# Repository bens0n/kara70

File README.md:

# kara70
70% FRL TKL keyboard assembled with primarily through hole components, including usb type-c. Inspired by cftkb [discipline](https://github.com/coseyfannitutti/discipline) and [mysterium](https://github.com/coseyfannitutti/mysterium), and also envious' [delirium](https://github.com/Envious-Data/Env-KB). 

The microcontroller has been updated from an atmega to an RP2040, which is mounted on the back-side to maintain the through-hole look. A slightly unnecessary logic shifter does double duty as a pretend through-hole controller. Underglow RGB has been added, and a minimal (LED diffusing) case connects the base to the plate.

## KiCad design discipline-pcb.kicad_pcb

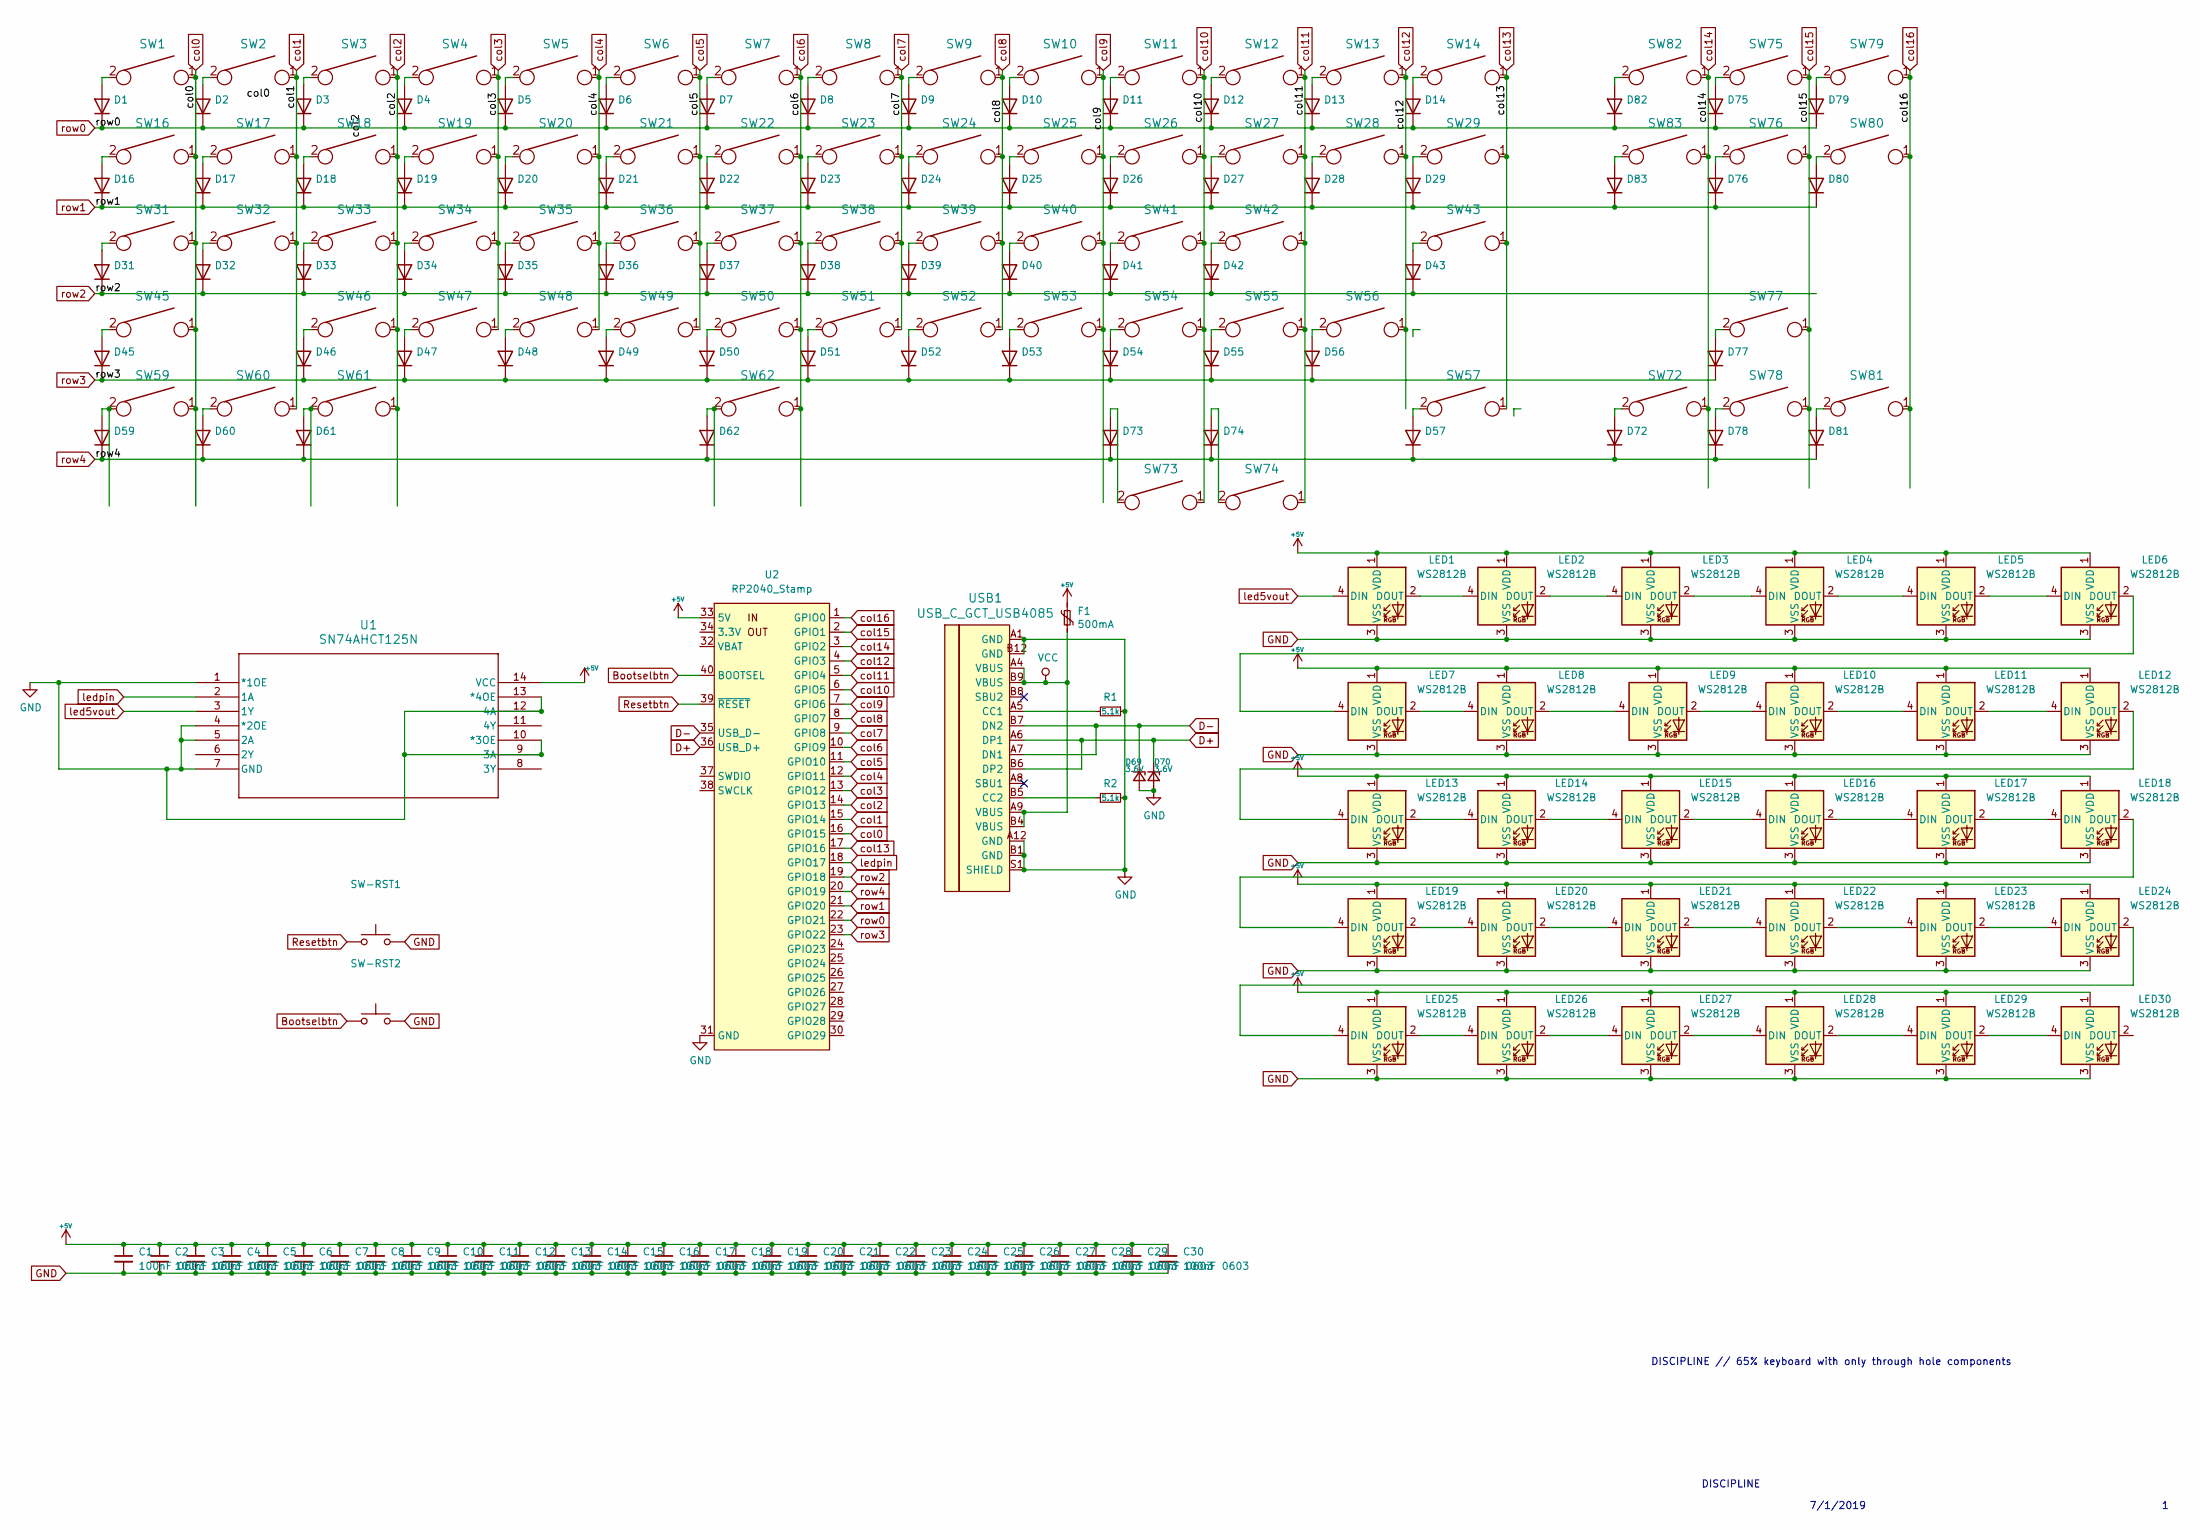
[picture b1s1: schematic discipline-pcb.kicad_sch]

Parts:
C1, C2, C3, C4, C5, C6, C7, C8, C9, C10, C11, C12, C13, C14, C15, C16, C17, C18, C19, C20, C21, C22, C23, C24, C25, C26, C27, C28, C29, C30: 100nF 0603; C_0603_1608Metric_Pad1.08x0.95mm_HandSolder
D1, D2, D3, D4, D5, D6, D7, D8, D9, D10, D11, D12, D13, D14, D16, D17, D18, D19, D20, D21, D22, D23, D24, D25, D26, D27, D28, D29, D31, D32, D33, D34, D35, D36, D37, D38, D39, D40, D41, D42, D43, D45, D46, D47, D48, D49, D50, D51, D52, D53, D54, D55, D56, D57, D59, D60, D61, D62, D72, D73, D74, D75, D76, D77, D78, D79, D80, D81, D82, D83: D_DO-35_SOD27_P5.08mm_Horizontal
D69, D70: 3.6V; D_DO-35_SOD27_P5.08mm_Horizontal
F1: 500mA; polyfuse_5.1mm
LED1, LED2, LED3, LED4, LED5, LED6, LED7, LED8, LED9, LED10, LED11, LED12, LED13, LED14, LED15, LED16, LED17, LED18, LED19, LED20, LED21, LED22, LED23, LED24, LED25, LED26, LED27, LED28, LED29, LED30: WS2812B; LED_WS2812B_PLCC4_5.0x5.0mm_P3.2mm
R1, R2: 5.1k; R_Axial_DIN0204_L3.6mm_D1.6mm_P7.62mm_Horizontal
SW1, SW2, SW3, SW4, SW5, SW6, SW7, SW8, SW9, SW10, SW11, SW12, SW13, SW17, SW18, SW19, SW20, SW21, SW22, SW23, SW24, SW25, SW26, SW27, SW28, SW32, SW33, SW34, SW35, SW36, SW37, SW38, SW39, SW40, SW41, SW42, SW46, SW47, SW48, SW49, SW50, SW51, SW52, SW53, SW54, SW55, SW72, SW75, SW76, SW77, SW78, SW79, SW80, SW81, SW82, SW83: KEYSW; MX-Hotswap-1U
SW14: KEYSW; MX-Hotswap-2U
SW16, SW29, SW73, SW74: KEYSW; MX-Hotswap-1.5U
SW31: KEYSW; MX-Hotswap-1.75U
SW43, SW45: KEYSW; MX-Hotswap-2.25U
SW56: KEYSW; MX-Hotswap-2.75U
SW57, SW59, SW60, SW61: KEYSW; MX-Hotswap-1.25U
SW62: KEYSW; MX-Hotswap-7U-ReversedStabilizers
SW-RST1, SW-RST2: SW_PUSH_6mm
U1: SN74AHCT125N; N14
U2: RP2040_Stamp; RP2xxx_Stamp_SMD
USB1: USB_C_GCT_USB4085

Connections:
+5V: C1.1, C2.1, C3.1, C4.1, C5.1, C6.1, C7.1, C8.1, C9.1, C10.1, C11.1, C12.1, C13.1, C14.1, C15.1, C16.1, C17.1, C18.1, C19.1, C20.1, C21.1, C22.1, C23.1, C24.1, C25.1, C26.1, C27.1, C28.1, C29.1, C30.1, F1.1, LED1.1 (VDD), LED2.1 (VDD), LED3.1 (VDD), LED4.1 (VDD), LED5.1 (VDD), LED6.1 (VDD), LED7.1 (VDD), LED8.1 (VDD), LED9.1 (VDD), LED10.1 (VDD), LED11.1 (VDD), LED12.1 (VDD), LED13.1 (VDD), LED14.1 (VDD), LED15.1 (VDD), LED16.1 (VDD), LED17.1 (VDD), LED18.1 (VDD), LED19.1 (VDD), LED20.1 (VDD), LED21.1 (VDD), LED22.1 (VDD), LED23.1 (VDD), LED24.1 (VDD), LED25.1 (VDD), LED26.1 (VDD), LED27.1 (VDD), LED28.1 (VDD), LED29.1 (VDD), LED30.1 (VDD), U1.14 (VCC), U2.33 (5V)
Bootselbtn: SW-RST2.1, U2.40 (BOOTSEL)
D+: D70.1 (K), U2.36 (USB_D+), USB1.A6 (DP1), USB1.B6 (DP2)
D-: D69.1 (K), U2.35 (USB_D-), USB1.A7 (DN1), USB1.B7 (DN2)
GND: C1.2, C2.2, C3.2, C4.2, C5.2, C6.2, C7.2, C8.2, C9.2, C10.2, C11.2, C12.2, C13.2, C14.2, C15.2, C16.2, C17.2, C18.2, C19.2, C20.2, C21.2, C22.2, C23.2, C24.2, C25.2, C26.2, C27.2, C28.2, C29.2, C30.2, D69.2 (A), D70.2 (A), LED1.3 (VSS), LED2.3 (VSS), LED3.3 (VSS), LED4.3 (VSS), LED5.3 (VSS), LED6.3 (VSS), LED7.3 (VSS), LED8.3 (VSS), LED9.3 (VSS), LED10.3 (VSS), LED11.3 (VSS), LED12.3 (VSS), LED13.3 (VSS), LED14.3 (VSS), LED15.3 (VSS), LED16.3 (VSS), LED17.3 (VSS), LED18.3 (VSS), LED19.3 (VSS), LED20.3 (VSS), LED21.3 (VSS), LED22.3 (VSS), LED23.3 (VSS), LED24.3 (VSS), LED25.3 (VSS), LED26.3 (VSS), LED27.3 (VSS), LED28.3 (VSS), LED29.3 (VSS), LED30.3 (VSS), R1.1, R2.2, SW-RST1.2, SW-RST2.2, U1.1 (*1OE), U1.4 (*2OE), U1.5 (2A), U1.7 (GND), U1.9 (3A), U1.10 (*3OE), U1.12 (4A), U1.13 (*4OE), U2.31 (GND), USB1.A1 (GND), USB1.A12 (GND), USB1.B1 (GND), USB1.B12 (GND), USB1.S1 (SHIELD)
unnamed: D1.2 (A), SW1.2
unnamed: D2.2 (A), SW2.2
unnamed: D3.2 (A), SW3.2
unnamed: D4.2 (A), SW4.2
unnamed: D5.2 (A), SW5.2
unnamed: D6.2 (A), SW6.2
unnamed: D7.2 (A), SW7.2
unnamed: D8.2 (A), SW8.2
unnamed: D9.2 (A), SW9.2
unnamed: D10.2 (A), SW10.2
unnamed: D11.2 (A), SW11.2
unnamed: D12.2 (A), SW12.2
unnamed: D13.2 (A), SW13.2
unnamed: D14.2 (A), SW14.2
unnamed: D16.2 (A), SW16.2
unnamed: D17.2 (A), SW17.2
unnamed: D18.2 (A), SW18.2
unnamed: D19.2 (A), SW19.2
unnamed: D20.2 (A), SW20.2
unnamed: D21.2 (A), SW21.2
unnamed: D22.2 (A), SW22.2
unnamed: D23.2 (A), SW23.2
unnamed: D24.2 (A), SW24.2
unnamed: D25.2 (A), SW25.2
unnamed: D26.2 (A), SW26.2
unnamed: D27.2 (A), SW27.2
unnamed: D28.2 (A), SW28.2
unnamed: D29.2 (A), SW29.2
unnamed: D31.2 (A), SW31.2
unnamed: D32.2 (A), SW32.2
unnamed: D33.2 (A), SW33.2
unnamed: D34.2 (A), SW34.2
unnamed: D35.2 (A), SW35.2
unnamed: D36.2 (A), SW36.2
unnamed: D37.2 (A), SW37.2
unnamed: D38.2 (A), SW38.2
unnamed: D39.2 (A), SW39.2
unnamed: D40.2 (A), SW40.2
unnamed: D41.2 (A), SW41.2
unnamed: D42.2 (A), SW42.2
unnamed: D43.2 (A), SW43.2
unnamed: D45.2 (A), SW45.2
unnamed: D46.2 (A), SW46.2
unnamed: D47.2 (A), SW47.2
unnamed: D48.2 (A), SW48.2
unnamed: D49.2 (A), SW49.2
unnamed: D50.2 (A), SW50.2
unnamed: D51.2 (A), SW51.2
unnamed: D52.2 (A), SW52.2
unnamed: D53.2 (A), SW53.2
unnamed: D54.2 (A), SW54.2
unnamed: D55.2 (A), SW55.2
unnamed: D56.2 (A), SW56.2
unnamed: D57.2 (A), SW57.2
unnamed: D59.2 (A), SW59.2
unnamed: D60.2 (A), SW60.2
unnamed: D61.2 (A), SW61.2
unnamed: D62.2 (A), SW62.2
unnamed: D72.2 (A), SW72.2
unnamed: D73.2 (A), SW73.2
unnamed: D74.2 (A), SW74.2
unnamed: D75.2 (A), SW75.2
unnamed: D76.2 (A), SW76.2
unnamed: D77.2 (A), SW77.2
unnamed: D78.2 (A), SW78.2
unnamed: D79.2 (A), SW79.2
unnamed: D80.2 (A), SW80.2
unnamed: D81.2 (A), SW81.2
unnamed: D82.2 (A), SW82.2
unnamed: D83.2 (A), SW83.2
unnamed: LED1.2 (DOUT), LED2.4 (DIN)
unnamed: LED2.2 (DOUT), LED3.4 (DIN)
unnamed: LED3.2 (DOUT), LED4.4 (DIN)
unnamed: LED4.2 (DOUT), LED5.4 (DIN)
unnamed: LED5.2 (DOUT), LED6.4 (DIN)
unnamed: LED6.2 (DOUT), LED7.4 (DIN)
unnamed: LED7.2 (DOUT), LED8.4 (DIN)
unnamed: LED8.2 (DOUT), LED9.4 (DIN)
unnamed: LED9.2 (DOUT), LED10.4 (DIN)
unnamed: LED10.2 (DOUT), LED11.4 (DIN)
unnamed: LED11.2 (DOUT), LED12.4 (DIN)
unnamed: LED12.2 (DOUT), LED13.4 (DIN)
unnamed: LED13.2 (DOUT), LED14.4 (DIN)
unnamed: LED14.2 (DOUT), LED15.4 (DIN)
unnamed: LED15.2 (DOUT), LED16.4 (DIN)
unnamed: LED16.2 (DOUT), LED17.4 (DIN)
unnamed: LED17.2 (DOUT), LED18.4 (DIN)
unnamed: LED18.2 (DOUT), LED19.4 (DIN)
unnamed: LED19.2 (DOUT), LED20.4 (DIN)
unnamed: LED20.2 (DOUT), LED21.4 (DIN)
unnamed: LED21.2 (DOUT), LED22.4 (DIN)
unnamed: LED22.2 (DOUT), LED23.4 (DIN)
unnamed: LED23.2 (DOUT), LED24.4 (DIN)
unnamed: LED24.2 (DOUT), LED25.4 (DIN)
unnamed: LED25.2 (DOUT), LED26.4 (DIN)
unnamed: LED26.2 (DOUT), LED27.4 (DIN)
unnamed: LED27.2 (DOUT), LED28.4 (DIN)
unnamed: LED28.2 (DOUT), LED29.4 (DIN)
unnamed: LED29.2 (DOUT), LED30.4 (DIN)
unnamed: R1.2, USB1.A5 (CC1)
unnamed: R2.1, USB1.B5 (CC2)
Resetbtn: SW-RST1.1, U2.39 (~RESET)
VCC: F1.2, USB1.A4 (VBUS), USB1.A9 (VBUS), USB1.B4 (VBUS), USB1.B9 (VBUS)
col0: SW1.1, SW16.1, SW31.1, SW45.1, SW59.1, U2.16 (GPIO15)
col1: SW2.1, SW17.1, SW32.1, SW60.1, U2.15 (GPIO14)
col2: SW3.1, SW18.1, SW33.1, SW46.1, SW61.1, U2.14 (GPIO13)
col3: SW4.1, SW19.1, SW34.1, SW47.1, U2.13 (GPIO12)
col4: SW5.1, SW20.1, SW35.1, SW48.1, U2.12 (GPIO11)
col5: SW6.1, SW21.1, SW36.1, SW49.1, U2.11 (GPIO10)
col6: SW7.1, SW22.1, SW37.1, SW50.1, SW62.1, U2.10 (GPIO9)
col7: SW8.1, SW23.1, SW38.1, SW51.1, U2.9 (GPIO8)
col8: SW9.1, SW24.1, SW39.1, SW52.1, U2.8 (GPIO7)
col9: SW10.1, SW25.1, SW40.1, SW53.1, U2.7 (GPIO6)
col10: SW11.1, SW26.1, SW41.1, SW54.1, SW73.1, U2.6 (GPIO5)
col11: SW12.1, SW27.1, SW42.1, SW55.1, SW74.1, U2.5 (GPIO4)
col12: SW13.1, SW28.1, SW56.1, U2.4 (GPIO3)
col13: SW14.1, SW29.1, SW43.1, SW57.1, U2.17 (GPIO16)
col14: SW72.1, SW82.1, SW83.1, U2.3 (GPIO2)
col15: SW75.1, SW76.1, SW77.1, SW78.1, U2.2 (GPIO1)
col16: SW79.1, SW80.1, SW81.1, U2.1 (GPIO0)
led5vout: LED1.4 (DIN), U1.3 (1Y)
ledpin: U1.2 (1A), U2.18 (GPIO17)
row0: D1.1 (K), D2.1 (K), D3.1 (K), D4.1 (K), D5.1 (K), D6.1 (K), D7.1 (K), D8.1 (K), D9.1 (K), D10.1 (K), D11.1 (K), D12.1 (K), D13.1 (K), D14.1 (K), D75.1 (K), D79.1 (K), D82.1 (K), U2.22 (GPIO21)
row1: D16.1 (K), D17.1 (K), D18.1 (K), D19.1 (K), D20.1 (K), D21.1 (K), D22.1 (K), D23.1 (K), D24.1 (K), D25.1 (K), D26.1 (K), D27.1 (K), D28.1 (K), D29.1 (K), D76.1 (K), D80.1 (K), D83.1 (K), U2.21 (GPIO20)
row2: D31.1 (K), D32.1 (K), D33.1 (K), D34.1 (K), D35.1 (K), D36.1 (K), D37.1 (K), D38.1 (K), D39.1 (K), D40.1 (K), D41.1 (K), D42.1 (K), D43.1 (K), U2.19 (GPIO18)
row3: D45.1 (K), D46.1 (K), D47.1 (K), D48.1 (K), D49.1 (K), D50.1 (K), D51.1 (K), D52.1 (K), D53.1 (K), D54.1 (K), D55.1 (K), D56.1 (K), D77.1 (K), U2.23 (GPIO22)
row4: D57.1 (K), D59.1 (K), D60.1 (K), D61.1 (K), D62.1 (K), D72.1 (K), D73.1 (K), D74.1 (K), D78.1 (K), D81.1 (K), U2.20 (GPIO19)

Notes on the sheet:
DISCIPLINE
DISCIPLINE // 65% keyboard with only through hole components
7/1/2019

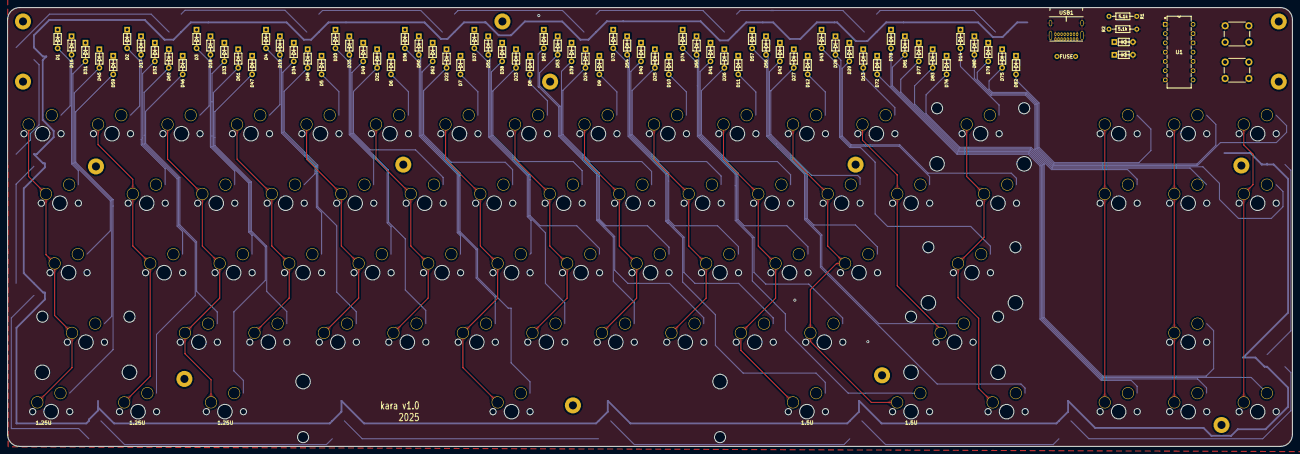
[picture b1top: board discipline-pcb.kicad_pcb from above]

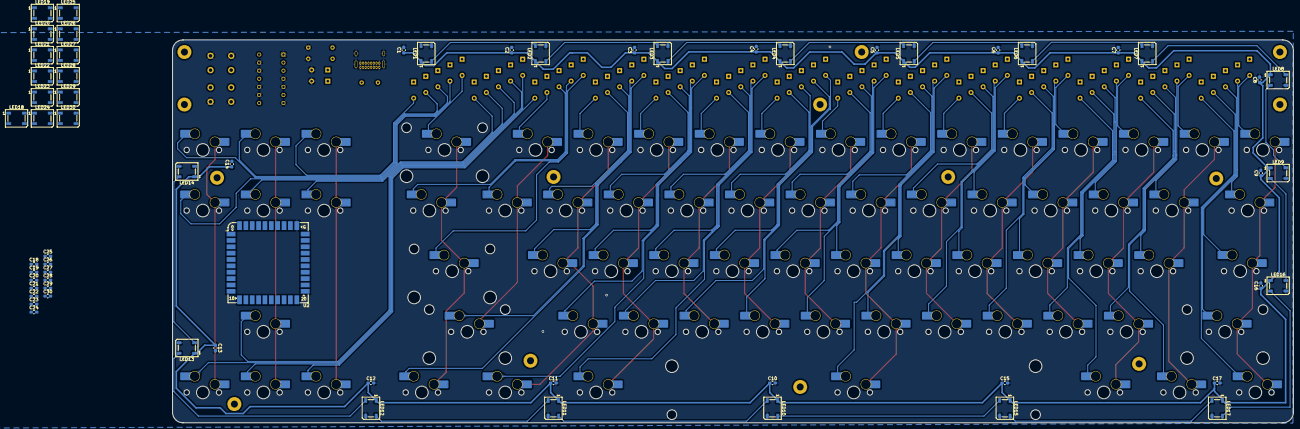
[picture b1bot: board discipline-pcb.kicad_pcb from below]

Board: 2 copper layers, 352.2 x 120.3 mm, 210 parts (131 on the bottom side), 132 nets.

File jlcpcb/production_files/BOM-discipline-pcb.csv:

Comment,Designator,Footprint,LCSC,Quantity
100nF 0805,"C1,C10,C11,C12,C13,C14,C15,C16,C17,C18,C19,C2,C20,C21,C22,C23,C24,C3,C4,C5,C6,C7,C8,C9",C_0805_2012Metric_Pad1.18x1.45mm_HandSolder,C28233,24
WS2812B,"LED1,LED10,LED11,LED12,LED13,LED14,LED15,LED16,LED17,LED18,LED19,LED2,LED20,LED21,LED22,LED23,LED24,LED3,LED4,LED5,LED6,LED7,LED8,LED9",LED_WS2812B_PLCC4_5.0x5.0mm_P3.2mm,C4154882,24
~,D1,D_DO-35_SOD27_P5.08mm_Horizontal,,1
~,D2,D_DO-35_SOD27_P5.08mm_Horizontal,,1
~,D3,D_DO-35_SOD27_P5.08mm_Horizontal,,1
~,D4,D_DO-35_SOD27_P5.08mm_Horizontal,,1
~,D5,D_DO-35_SOD27_P5.08mm_Horizontal,,1
~,D6,D_DO-35_SOD27_P5.08mm_Horizontal,,1
~,D7,D_DO-35_SOD27_P5.08mm_Horizontal,,1
~,D8,D_DO-35_SOD27_P5.08mm_Horizontal,,1
~,D9,D_DO-35_SOD27_P5.08mm_Horizontal,,1
~,D10,D_DO-35_SOD27_P5.08mm_Horizontal,,1
~,D11,D_DO-35_SOD27_P5.08mm_Horizontal,,1
~,D12,D_DO-35_SOD27_P5.08mm_Horizontal,,1
~,D13,D_DO-35_SOD27_P5.08mm_Horizontal,,1
~,D14,D_DO-35_SOD27_P5.08mm_Horizontal,,1
~,D16,D_DO-35_SOD27_P5.08mm_Horizontal,,1
~,D17,D_DO-35_SOD27_P5.08mm_Horizontal,,1
~,D18,D_DO-35_SOD27_P5.08mm_Horizontal,,1
~,D19,D_DO-35_SOD27_P5.08mm_Horizontal,,1
~,D20,D_DO-35_SOD27_P5.08mm_Horizontal,,1
~,D21,D_DO-35_SOD27_P5.08mm_Horizontal,,1
~,D22,D_DO-35_SOD27_P5.08mm_Horizontal,,1
~,D23,D_DO-35_SOD27_P5.08mm_Horizontal,,1
~,D24,D_DO-35_SOD27_P5.08mm_Horizontal,,1
~,D25,D_DO-35_SOD27_P5.08mm_Horizontal,,1
~,D26,D_DO-35_SOD27_P5.08mm_Horizontal,,1
~,D27,D_DO-35_SOD27_P5.08mm_Horizontal,,1
~,D28,D_DO-35_SOD27_P5.08mm_Horizontal,,1
~,D29,D_DO-35_SOD27_P5.08mm_Horizontal,,1
~,D31,D_DO-35_SOD27_P5.08mm_Horizontal,,1
~,D32,D_DO-35_SOD27_P5.08mm_Horizontal,,1
~,D33,D_DO-35_SOD27_P5.08mm_Horizontal,,1
~,D34,D_DO-35_SOD27_P5.08mm_Horizontal,,1
~,D35,D_DO-35_SOD27_P5.08mm_Horizontal,,1
~,D36,D_DO-35_SOD27_P5.08mm_Horizontal,,1
~,D37,D_DO-35_SOD27_P5.08mm_Horizontal,,1
~,D38,D_DO-35_SOD27_P5.08mm_Horizontal,,1
~,D39,D_DO-35_SOD27_P5.08mm_Horizontal,,1
~,D40,D_DO-35_SOD27_P5.08mm_Horizontal,,1
~,D41,D_DO-35_SOD27_P5.08mm_Horizontal,,1
~,D42,D_DO-35_SOD27_P5.08mm_Horizontal,,1
~,D43,D_DO-35_SOD27_P5.08mm_Horizontal,,1
~,D45,D_DO-35_SOD27_P5.08mm_Horizontal,,1
~,D46,D_DO-35_SOD27_P5.08mm_Horizontal,,1
~,D47,D_DO-35_SOD27_P5.08mm_Horizontal,,1
~,D48,D_DO-35_SOD27_P5.08mm_Horizontal,,1
~,D49,D_DO-35_SOD27_P5.08mm_Horizontal,,1
~,D50,D_DO-35_SOD27_P5.08mm_Horizontal,,1
~,D51,D_DO-35_SOD27_P5.08mm_Horizontal,,1
~,D52,D_DO-35_SOD27_P5.08mm_Horizontal,,1
~,D53,D_DO-35_SOD27_P5.08mm_Horizontal,,1
~,D54,D_DO-35_SOD27_P5.08mm_Horizontal,,1
~,D55,D_DO-35_SOD27_P5.08mm_Horizontal,,1
~,D56,D_DO-35_SOD27_P5.08mm_Horizontal,,1
~,D59,D_DO-35_SOD27_P5.08mm_Horizontal,,1
~,D60,D_DO-35_SOD27_P5.08mm_Horizontal,,1
~,D61,D_DO-35_SOD27_P5.08mm_Horizontal,,1
~,D62,D_DO-35_SOD27_P5.08mm_Horizontal,,1
~,D73,D_DO-35_SOD27_P5.08mm_Horizontal,,1
~,D74,D_DO-35_SOD27_P5.08mm_Horizontal,,1
~,D79,D_DO-35_SOD27_P5.08mm_Horizontal,,1
SN74AHCT125N,U1,N14,,1
~,D75,D_DO-35_SOD27_P5.08mm_Horizontal,,1
3.6V,D70,D_DO-35_SOD27_P5.08mm_Horizontal,,1
USB_C_GCT_USB4085,USB1,USB_C_GCT_USB4085,,1
5.1k,R2,R_Axial_DIN0204_L3.6mm_D1.6mm_P7.62mm_Horizontal,,1
~,D81,D_DO-35_SOD27_P5.08mm_Horizontal,,1
~,D83,D_DO-35_SOD27_P5.08mm_Horizontal,,1
~,D57,D_DO-35_SOD27_P5.08mm_Horizontal,,1
~,D82,D_DO-35_SOD27_P5.08mm_Horizontal,,1
5.1k,R1,R_Axial_DIN0204_L3.6mm_D1.6mm_P7.62mm_Horizontal,,1
~,D76,D_DO-35_SOD27_P5.08mm_Horizontal,,1
~,D77,D_DO-35_SOD27_P5.08mm_Horizontal,,1
500mA,F1,polyfuse_5.1mm,,1
~,D72,D_DO-35_SOD27_P5.08mm_Horizontal,,1
3.6V,D69,D_DO-35_SOD27_P5.08mm_Horizontal,,1
~,D78,D_DO-35_SOD27_P5.08mm_Horizontal,,1
~,D80,D_DO-35_SOD27_P5.08mm_Horizontal,,1
KEYSW,SW1,MX-Hotswap-1U,,1
KEYSW,SW2,MX-Hotswap-1U,,1
KEYSW,SW3,MX-Hotswap-1U,,1
KEYSW,SW4,MX-Hotswap-1U,,1
KEYSW,SW5,MX-Hotswap-1U,,1
KEYSW,SW6,MX-Hotswap-1U,,1
KEYSW,SW7,MX-Hotswap-1U,,1
KEYSW,SW8,MX-Hotswap-1U,,1
KEYSW,SW9,MX-Hotswap-1U,,1
KEYSW,SW10,MX-Hotswap-1U,,1
KEYSW,SW11,MX-Hotswap-1U,,1
KEYSW,SW12,MX-Hotswap-1U,,1
KEYSW,SW13,MX-Hotswap-1U,,1
KEYSW,SW17,MX-Hotswap-1U,,1
KEYSW,SW18,MX-Hotswap-1U,,1
KEYSW,SW19,MX-Hotswap-1U,,1
KEYSW,SW20,MX-Hotswap-1U,,1
KEYSW,SW21,MX-Hotswap-1U,,1
KEYSW,SW22,MX-Hotswap-1U,,1
KEYSW,SW23,MX-Hotswap-1U,,1
KEYSW,SW24,MX-Hotswap-1U,,1
KEYSW,SW25,MX-Hotswap-1U,,1
KEYSW,SW26,MX-Hotswap-1U,,1
KEYSW,SW27,MX-Hotswap-1U,,1
KEYSW,SW28,MX-Hotswap-1U,,1
KEYSW,SW32,MX-Hotswap-1U,,1
KEYSW,SW33,MX-Hotswap-1U,,1
KEYSW,SW34,MX-Hotswap-1U,,1
KEYSW,SW35,MX-Hotswap-1U,,1
KEYSW,SW36,MX-Hotswap-1U,,1
KEYSW,SW37,MX-Hotswap-1U,,1
KEYSW,SW38,MX-Hotswap-1U,,1
KEYSW,SW39,MX-Hotswap-1U,,1
KEYSW,SW40,MX-Hotswap-1U,,1
KEYSW,SW41,MX-Hotswap-1U,,1
KEYSW,SW42,MX-Hotswap-1U,,1
KEYSW,SW46,MX-Hotswap-1U,,1
KEYSW,SW47,MX-Hotswap-1U,,1
KEYSW,SW48,MX-Hotswap-1U,,1
KEYSW,SW49,MX-Hotswap-1U,,1
KEYSW,SW50,MX-Hotswap-1U,,1
KEYSW,SW51,MX-Hotswap-1U,,1
KEYSW,SW52,MX-Hotswap-1U,,1
KEYSW,SW53,MX-Hotswap-1U,,1
KEYSW,SW54,MX-Hotswap-1U,,1
KEYSW,SW55,MX-Hotswap-1U,,1
KEYSW,SW62,MX-Hotswap-7U-ReversedStabilizers,,1
KEYSW,SW14,MX-Hotswap-2U,,1
KEYSW,SW29,MX-Hotswap-1.5U,,1
KEYSW,SW31,MX-Hotswap-1.75U,,1
KEYSW,SW43,MX-Hotswap-2.25U,,1
KEYSW,SW45,MX-Hotswap-2.25U,,1
KEYSW,SW56,MX-Hotswap-2.75U,,1
KEYSW,SW59,MX-Hotswap-1.25U,,1
KEYSW,SW60,MX-Hotswap-1.25U,,1
KEYSW,SW61,MX-Hotswap-1.25U,,1
KEYSW,SW73,MX-Hotswap-1.5U,,1
KEYSW,SW74,MX-Hotswap-1.5U,,1
KEYSW,SW16,MX-Hotswap-1.5U,,1
KEYSW,SW82,MX-Hotswap-1U,,1
KEYSW,SW80,MX-Hotswap-1U,,1
KEYSW,SW83,MX-Hotswap-1U,,1
KEYSW,SW81,MX-Hotswap-1U,,1
KEYSW,SW76,MX-Hotswap-1U,,1
KEYSW,SW72,MX-Hotswap-1U,,1
KEYSW,SW79,MX-Hotswap-1U,,1
KEYSW,SW77,MX-Hotswap-1U,,1
KEYSW,SW57,MX-Hotswap-1.25U,,1
KEYSW,SW78,MX-Hotswap-1U,,1
KEYSW,SW75,MX-Hotswap-1U,,1
RP2040_Stamp,U2,RP2xxx_Stamp_SMD,,1

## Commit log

2025-02-21 initial upgrade to kicad 8
2025-02-24 add a controller
2025-02-24 continue to plat
2025-02-24 use sensible matrix
2025-02-24 more jazz
2025-02-24 soldermask color
2025-02-24 more routing
2025-02-24 jazzbjazz
2025-02-24 sort spacings and fix
2025-02-25 add stabs, update footprint for cpico
2025-02-25 before changing to top-strip
2025-02-25 significant improvements to placement
2025-02-25 gross layout looking better
2025-02-25 starting to look like something
2025-02-26 add continuation marks aping diodes
2025-02-26 routing
2025-02-26 update nets
2025-02-26 add dru
2025-02-26 update dru
2025-02-26 UPDATE KARA
2025-02-26 vias
2025-02-26 ignore zip
2025-02-26 add mounting points
2025-03-01 unsure - potentially revert?
2025-03-01 update to hotswap; needs rerouting
2025-03-02 add level shifter for a laugh
2025-03-02 add decoupling caps
2025-03-02 update led labels
2025-03-02 add leds to pcb
2025-03-03 add 3d model to level shifter
2025-03-03 move some leds
2025-03-03 who knows
2025-03-03 place some nets; perhaps screw up the nets
2025-03-04 update footprints for solder+hotswap
2025-03-04 before routing LEDs
2025-03-04 update to teardrops
2025-03-04 unroute everything :(
2025-03-04 rotate led footprints
2025-03-04 basic LED routing
2025-03-04 at point of q's
2025-03-05 move controller
2025-03-05 add submodule for stamp
2025-03-05 after advice on usb implementation
2025-03-05 remove redundant resistors
2025-03-05 continue routing and adding LEDs
2025-03-05 more led routing
2025-03-05 leds placed, diodes and MCU left...
2025-03-06 move to 0805
2025-03-06 update 3d models
2025-03-06 move origin to top-left switch for easy comparison
2025-03-06 tiny tweaks [17um] to position of a couple of switches
2025-03-06 test jlcpcb export plugin
2025-03-06 add jlcpcb part mapping
2025-03-07 update kle to reflect true position of nav cluster
2025-03-09 annotate KLE for matrix
2025-03-10 cad files
2025-03-10 update kle
2025-03-11 export additional step file and remove old files
2025-03-11 very simple base implementation
2025-03-11 update naming to kara
2025-03-11 update base to match holes in pcb
2025-03-11 add kicad plate
2025-03-11 regenerate all gerbers
2025-03-11 remove outdated BOM
2025-03-12 add v1 case files
2025-03-18 add via fw details
2025-03-21 update via keymap and remove detritus
2025-03-21 fix incorrect up/down rgblighting keymap
